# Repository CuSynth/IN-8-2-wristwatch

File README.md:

Not completed project. Here I want to make IN-8-2 based wristwatch. This is just the beginning of the project, so there might be some mistakes in PCB.

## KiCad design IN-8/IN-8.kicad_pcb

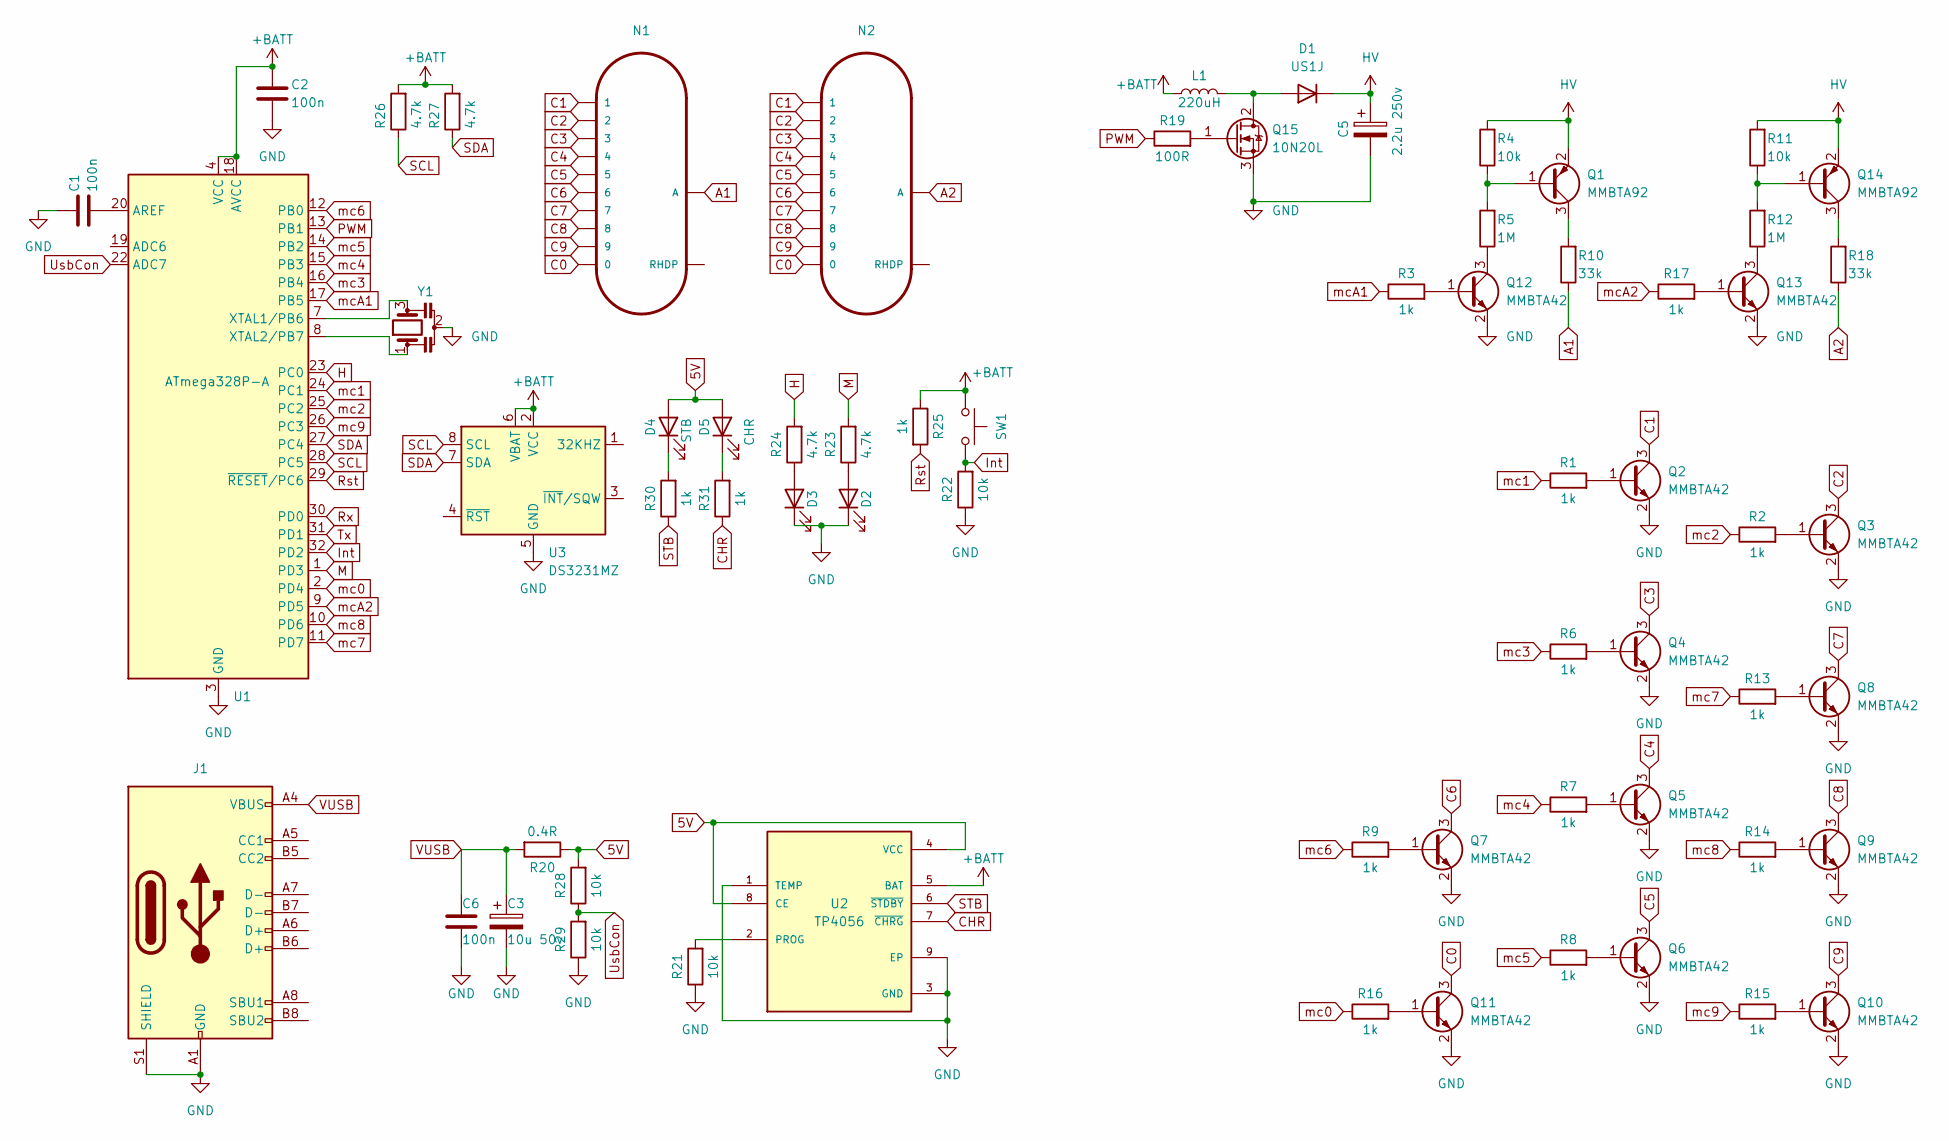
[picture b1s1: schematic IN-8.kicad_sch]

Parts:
C1, C2, C6: 100n; C_0805_2012Metric
C3: 10u 50v; CP_Radial_D5.0mm_P2.00mm
C5: 2.2u 250v; CP_Radial_D6.3mm_P2.50mm
D1: US1J; D_SMA
D2, D3: LED; LED_D3.0mm_Clear
D4: STB; LED_0805_2012Metric
D5: CHR; LED_0805_2012Metric
J1: USB_C_Receptacle_USB2.0; USB_C_Receptacle_JAE_DX07S016JA1R1500
L1: 220uH; L_Radial_D7.0mm_P3.00mm
N1, N2: IN-8-2
Q1, Q14: MMBTA92; SOT-23
Q2, Q3, Q4, Q5, Q6, Q7, Q8, Q9, Q10, Q11, Q12, Q13: MMBTA42; SOT-23
Q15: 10N20L; TO-252-2
R1, R2, R3, R6, R7, R8, R9, R13, R14, R15, R16, R17, R25, R30, R31: 1k; R_0805_2012Metric
R4, R11, R21, R22, R28, R29: 10k; R_0805_2012Metric
R5, R12: 1M; R_0805_2012Metric
R10, R18: 33k; R_0805_2012Metric
R19: 100R; R_0805_2012Metric
R20: 0.4R; R_0805_2012Metric
R23, R24, R26, R27: 4.7k; R_0805_2012Metric
SW1: SW_Push; SW_Tactile_SKHH_Angled
U1: ATmega328P-A; TQFP-32_7x7mm_P0.8mm
U2: TP4056; SOP127P600X175-9N
U3: DS3231MZ; SOIC-8_3.9x4.9mm_P1.27mm
Y1: Resonator; Resonator_SMD_Murata_CSTxExxV-3Pin_3.0x1.1mm

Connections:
5V: D4.2 (A), D5.2 (A), R20.1, R28.2, U2.4 (VCC), U2.8 (CE)
+BATT: C2.1, L1.1, R25.1, R26.2, R27.2, SW1.1, U1.4 (VCC), U1.6 (VCC), U1.18 (AVCC), U2.5 (BAT), U3.2 (VCC), U3.6 (VBAT); also elsewhere on the board
A1: N1.A, R10.1
A2: N2.A, R18.1
C0: N1.0, N2.0, Q11.3 (C)
C1: N1.1, N2.1, Q2.3 (C)
C2: N1.2, N2.2, Q3.3 (C)
C3: N1.3, N2.3, Q4.3 (C)
C4: N1.4, N2.4, Q5.3 (C)
C5: N1.5, N2.5, Q6.3 (C)
C6: N1.6, N2.6, Q7.3 (C)
C7: N1.7, N2.7, Q8.3 (C)
C8: N1.8, N2.8, Q9.3 (C)
C9: N1.9, N2.9, Q10.3 (C)
CHR: R31.1, U2.7 (~CHRG)
GND: C1.1, C2.2, C3.2, C5.2, C6.2, D2.1 (K), D3.1 (K), J1.A1 (GND), J1.A12 (GND), J1.B1 (GND), J1.B12 (GND), J1.S1 (SHIELD), Q2.2 (E), Q3.2 (E), Q4.2 (E), Q5.2 (E), Q6.2 (E), Q7.2 (E), Q8.2 (E), Q9.2 (E), Q10.2 (E), Q11.2 (E), Q12.2 (E), Q13.2 (E), Q15.3 (S), R21.1, R22.1, R29.1, U1.3 (GND), U1.5 (GND), U1.21 (GND), U2.1 (TEMP), U2.3 (GND), U2.9 (EP), U3.5 (GND), Y1.2; also elsewhere on the board
H: R24.2, U1.23 (PC0)
HV: C5.1, D1.1 (K), Q1.2 (E), Q14.2 (E), R4.2, R11.2
Int: R22.2, SW1.2, U1.32 (PD2)
M: R23.2, U1.1 (PD3)
unnamed: C1.2, U1.20 (AREF)
unnamed 21: D1.2 (A), L1.2, Q15.2 (D); also elsewhere on the board
unnamed: D2.2 (A), R23.1
unnamed: D3.2 (A), R24.1
unnamed: D4.1 (K), R30.2
unnamed: D5.1 (K), R31.2
unnamed: Q1.1 (B), R4.1, R5.2
unnamed: Q1.3 (C), R10.2
unnamed: Q2.1 (B), R1.2
unnamed: Q3.1 (B), R2.2
unnamed: Q4.1 (B), R6.2
unnamed: Q5.1 (B), R7.2
unnamed: Q6.1 (B), R8.2
unnamed: Q7.1 (B), R9.2
unnamed: Q8.1 (B), R13.2
unnamed: Q9.1 (B), R14.2
unnamed: Q10.1 (B), R15.2
unnamed: Q11.1 (B), R16.2
unnamed: Q12.1 (B), R3.2
unnamed: Q12.3 (C), R5.1
unnamed: Q13.1 (B), R17.2
unnamed: Q13.3 (C), R12.1
unnamed: Q14.1 (B), R11.1, R12.2
unnamed: Q14.3 (C), R18.2
unnamed: Q15.1 (G), R19.2
unnamed: R21.2, U2.2 (PROG)
unnamed: U1.7 (XTAL1/PB6), Y1.3
unnamed: U1.8 (XTAL2/PB7), Y1.1
PWM: R19.1, U1.13 (PB1)
Rst: R25.2, U1.29 (~RESET/PC6); also elsewhere on the board
Rx: U1.30 (PD0); also elsewhere on the board
SCL: R26.1, U1.28 (PC5), U3.8 (SCL)
SDA: R27.1, U1.27 (PC4), U3.7 (SDA)
STB: R30.1, U2.6 (~STDBY)
Tx: U1.31 (PD1); also elsewhere on the board
UsbCon: R28.1, R29.2, U1.22 (ADC7)
VUSB: C3.1, C6.1, J1.A4 (VBUS), J1.A9 (VBUS), J1.B4 (VBUS), J1.B9 (VBUS), R20.2
mc0: R16.1, U1.2 (PD4)
mc1: R1.1, U1.24 (PC1)
mc2: R2.1, U1.25 (PC2)
mc3: R6.1, U1.16 (PB4)
mc4: R7.1, U1.15 (PB3)
mc5: R8.1, U1.14 (PB2)
mc6: R9.1, U1.12 (PB0)
mc7: R13.1, U1.11 (PD7)
mc8: R14.1, U1.10 (PD6)
mc9: R15.1, U1.26 (PC3)
mcA1: R3.1, U1.17 (PB5)
mcA2: R17.1, U1.9 (PD5)

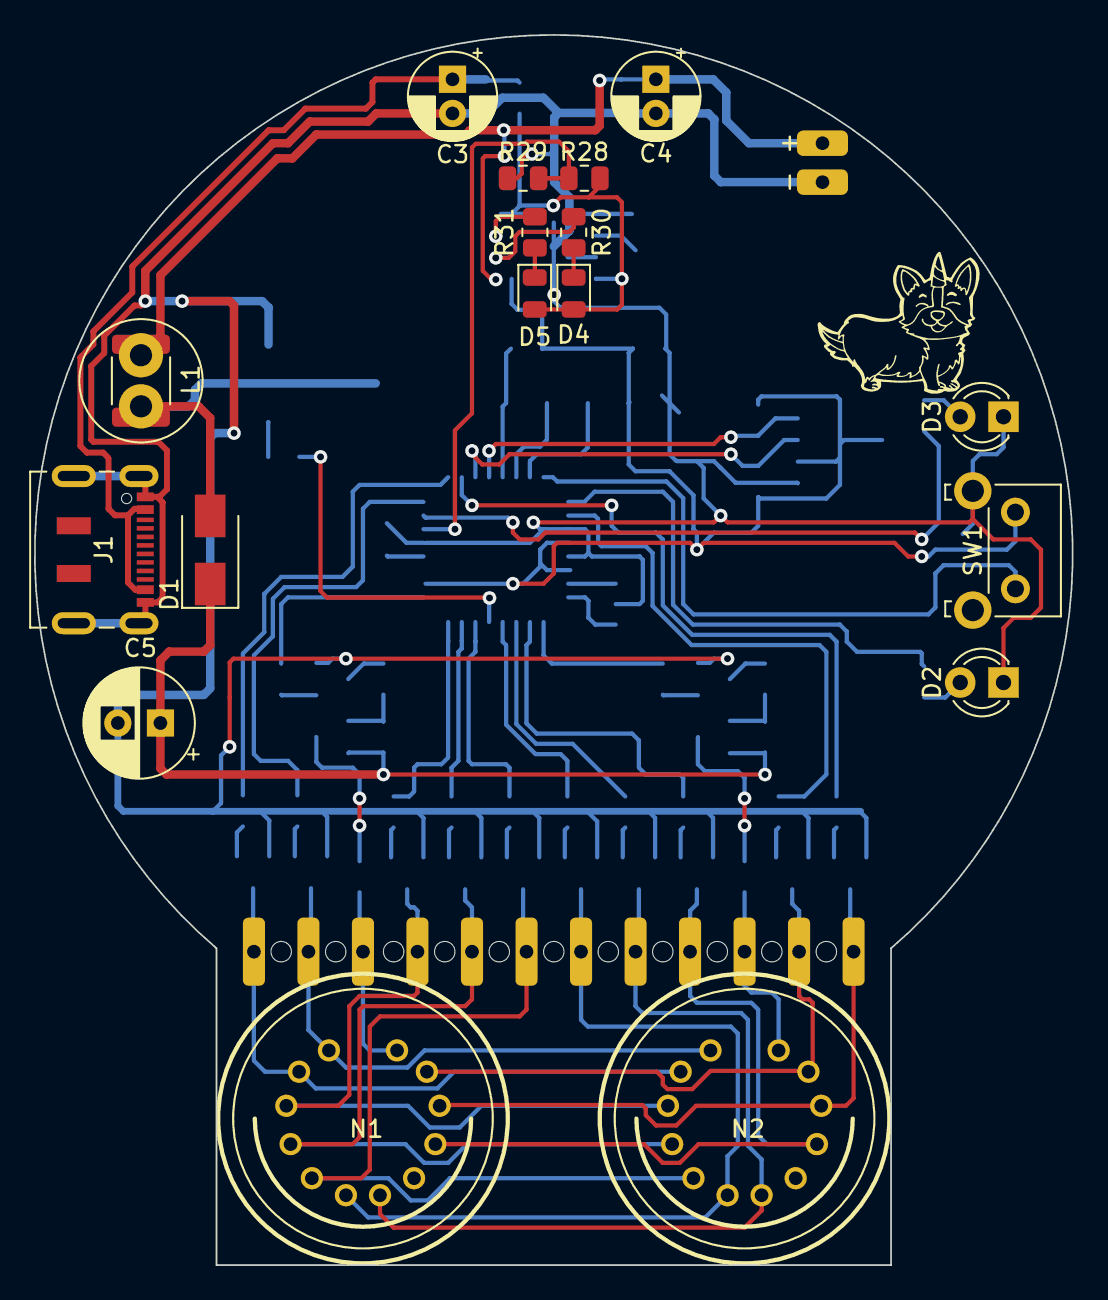
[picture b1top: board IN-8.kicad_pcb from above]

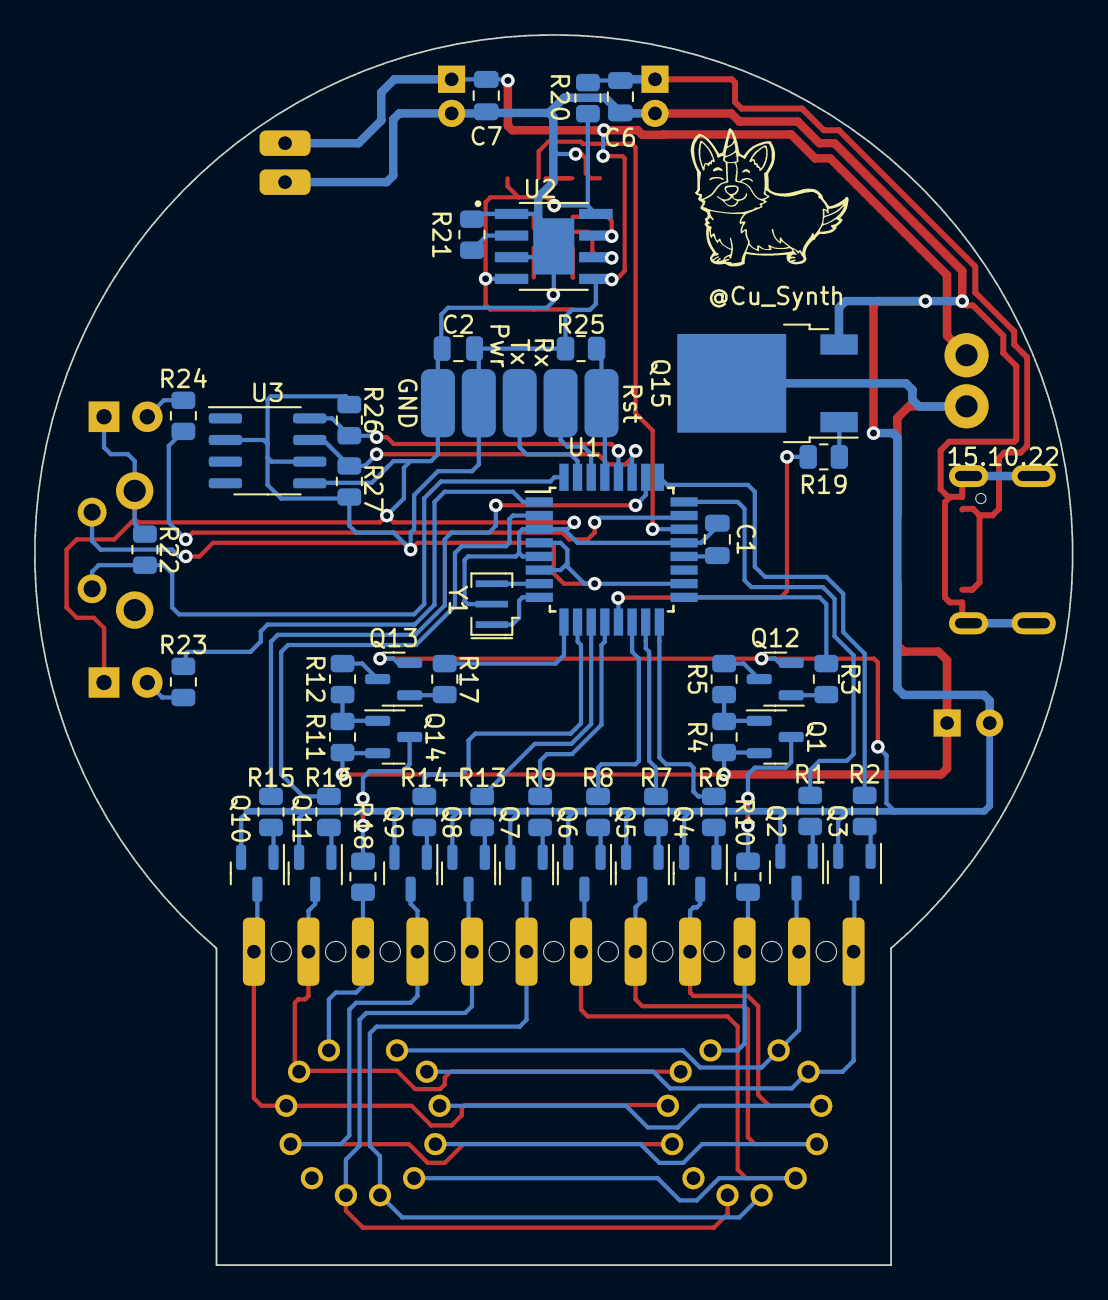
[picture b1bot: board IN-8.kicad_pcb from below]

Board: 2 copper layers, 60.9 x 72.2 mm, 75 parts (55 on the bottom side), 69 nets.

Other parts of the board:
+: SolderWirePad_1x01_SMD_1x2mm
-: SolderWirePad_1x01_SMD_1x2mm
C4: 10u 50v; CP_Radial_D5.0mm_P2.00mm
C7: 100n; C_0805_2012Metric
GND: SolderWirePad_1x01_SMD_1x2mm
L2: 220uH; L_1812_4532Metric
Pwr: SolderWirePad_1x01_SMD_1x2mm
Rst: SolderWirePad_1x01_SMD_1x2mm
Rx: SolderWirePad_1x01_SMD_1x2mm
Tx: SolderWirePad_1x01_SMD_1x2mm

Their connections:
+BATT: +.1, C4.1, C7.1, L2.1, Pwr.1; also elsewhere on the board
GND: -.1, C4.2, C7.2, GND.1; also elsewhere on the board
unnamed 21: L2.2; also elsewhere on the board
Rst: Rst.1; also elsewhere on the board
Rx: Rx.1; also elsewhere on the board
Tx: Tx.1; also elsewhere on the board

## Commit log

2022-09-16 PCB and firmware are here now
2022-09-16 Readme is here
2022-09-16 Pictures are here
2022-09-16 Picturea added to the Readme
2022-09-16 Some new pictures
2023-08-11 Test firmware is here
2023-08-11 KiCad project updaated, gitignore added
2023-08-11 Dynamic indication and sleep test lazy implementation
2023-08-30 Low level GPIO implementation
2023-08-30 Low level GPIO used. Time mode implemented
2023-08-30 Dynamic indication by timer is used
2023-08-30 Refactored
2023-08-31 Supply_voltage mode is here
2023-08-31 Time set implemented
2023-09-01 Now you can turn the animation on and off
2023-11-28 OnPower constant mode implementation
